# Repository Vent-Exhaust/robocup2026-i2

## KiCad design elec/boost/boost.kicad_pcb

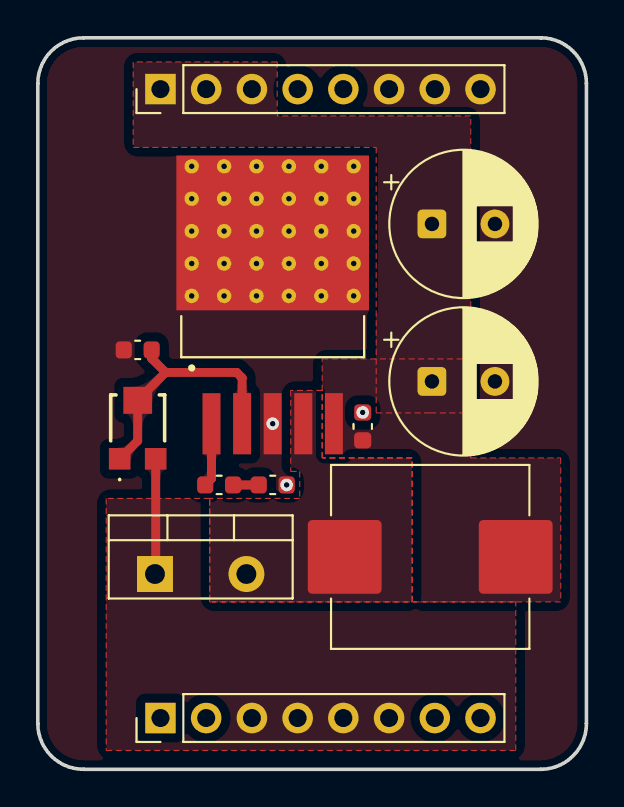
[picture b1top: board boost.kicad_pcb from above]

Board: 2 copper layers, 30.5 x 40.6 mm, 12 parts (0 on the bottom side), 7 nets.

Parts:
C1, C36: 100uF; CP_Radial_D8.0mm_P3.50mm
C35: 0.1uF; C_0603_1608Metric
C40: 0.68uF; C_0603_1608Metric
D2: MBR745; TO-220-2_Vertical
J1, J2: Conn_01x08; PinHeader_1x08_P2.54mm_Vertical
L33: 33uH; L_APV_APH1040
R36: 2K/2.94k; C_0603_1608Metric
R38: 3K; C_0603_1608Metric
U1: LM2587S-ADJ; VREG_TPS79625KTTR
VR1: TC33X-2-104E; TC33X2104E

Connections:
+12V: C1.1, C35.1, C36.1, J1.1, J1.2, J1.3, L33.1, U1.5 (VIN)
+24V: D2.1 (K), J2.3, J2.4, J2.5, J2.6, VR1.3
GND: C1.2, C35.2, C36.2, C40.2, J1.6, J1.7, J1.8, R36.2, U1.3 (GND), U1.6 (GND)
unnamed: C40.1, R38.2
unnamed: D2.2 (A), L33.2, U1.4 (SW)
unnamed: R38.1, U1.1 (COMP)
unnamed: R36.1, U1.2 (FB), VR1.1, VR1.2

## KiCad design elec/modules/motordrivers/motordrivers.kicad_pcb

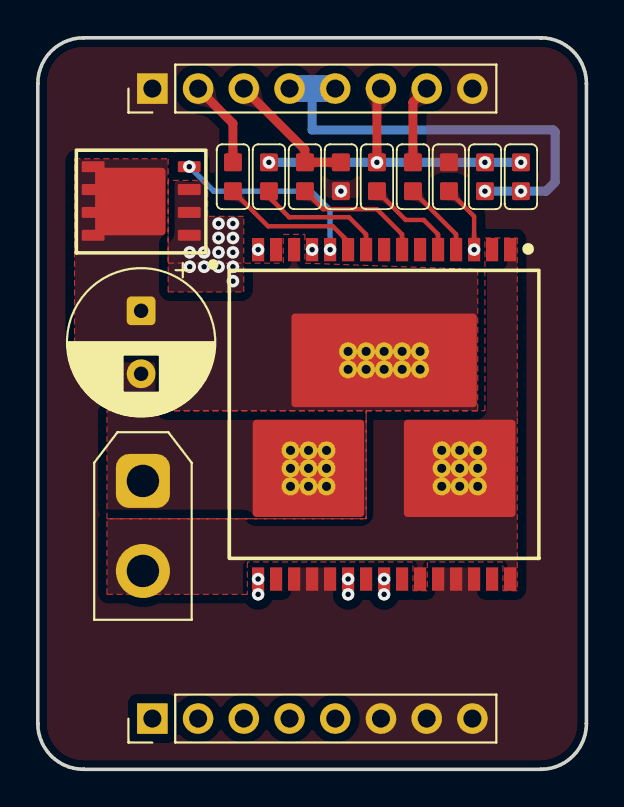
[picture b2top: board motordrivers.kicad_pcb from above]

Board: 2 copper layers, 30.5 x 40.6 mm, 15 parts (0 on the bottom side), 16 nets.

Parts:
C15: 470u; CP_Radial_D8.0mm_P3.50mm
C16: 0u1; Capacitor_0603
IC2: VNH5019ATR-E; VNH5019A-E custom
J1: Conn_01x02; AMASS_XT30UPB-F_1x02_P5.0mm_Vertical
J2, J3: Conn_01x08; PinHeader_1x08_P2.54mm_Vertical
Q1: AON6354; 8-DFN (5x6)withzedot
R8, R9: 3K3; Resistor_0603
R10, R11, R12, R13, R14: 1K; Resistor_0603
R15: 10K; Resistor_0603

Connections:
+3V3: J2.4, J2.5, R8.2, R9.2
+12V: IC2.12 (VBAT), J3.1, J3.2, J3.3, Q1.1 (S), Q1.2 (S), Q1.3 (S)
/CPM1: IC2.11 (CP), Q1.4 (G)
/M IN A: J2.7, R12.1
/M IN B: J2.2, R13.1
/M PWM: J2.3, R14.1, R15.1
/M SW: J2.6, R8.1, R9.1, R10.1, R11.1
/OUT A M: IC2.1 (OUTA), IC2.25 (OUTA), IC2.30 (OUTA), IC2.31 (OUTA), J1.2
/OUT B M: IC2.15 (OUTB), IC2.16 (OUTB), IC2.21 (OUTB), IC2.32 (OUTB), J1.1
GND: C15.2, C16.2, IC2.18 (GND), IC2.19 (GND), IC2.20 (GND), IC2.26 (GND), IC2.27 (GND), IC2.28 (GND), J2.1, J2.8, J3.6, J3.7, J3.8, R15.2
unnamed: C15.1, C16.1, IC2.3 (VCC), IC2.13 (VCC), IC2.23 (VCC), IC2.33 (VCC), Q1.5 (D), Q1.6 (D), Q1.7 (D), Q1.8 (D), Q1.9 (D)
unnamed: IC2.5 (ENA/DIAGA), R10.2
unnamed: IC2.9 (ENB/DIAGB), R11.2
unnamed: IC2.4 (INA), R12.2
unnamed: IC2.10 (INB), R13.2
unnamed: IC2.7 (PWM), R14.2

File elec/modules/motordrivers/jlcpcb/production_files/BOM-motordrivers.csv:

Comment,Designator,Footprint,LCSC,Quantity
0u1,C16,Capacitor_0603,C3011705,1
10K,R15,Resistor_0603,C25804,1
1K,"R10,R11,R12,R13,R14",Resistor_0603,C21190,5
3K3,"R8,R9",Resistor_0603,C22978,2
AON6354,Q1,8-DFN (5x6)withzedot,C22367225,1
VNH5019ATR-E,IC2,VNH5019A-E custom,C2653552,1

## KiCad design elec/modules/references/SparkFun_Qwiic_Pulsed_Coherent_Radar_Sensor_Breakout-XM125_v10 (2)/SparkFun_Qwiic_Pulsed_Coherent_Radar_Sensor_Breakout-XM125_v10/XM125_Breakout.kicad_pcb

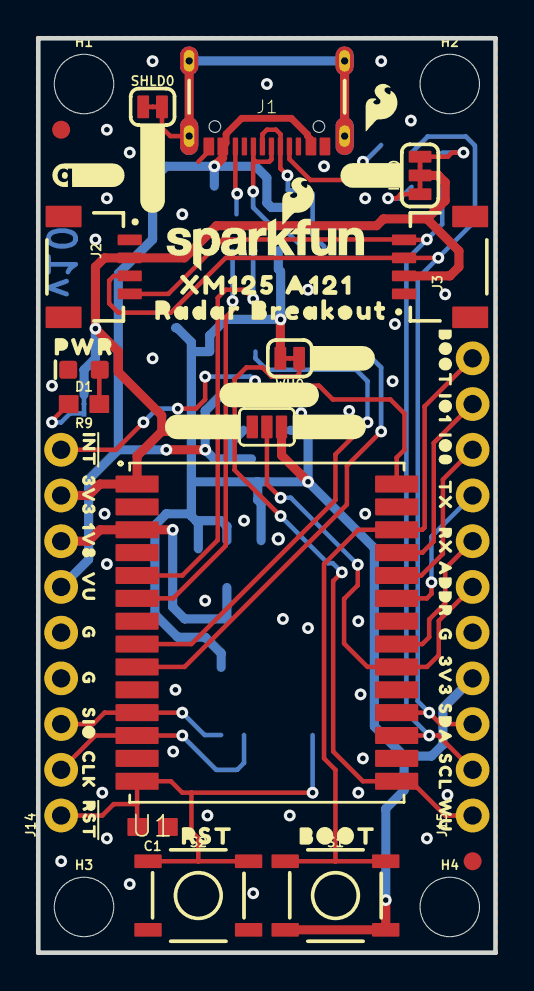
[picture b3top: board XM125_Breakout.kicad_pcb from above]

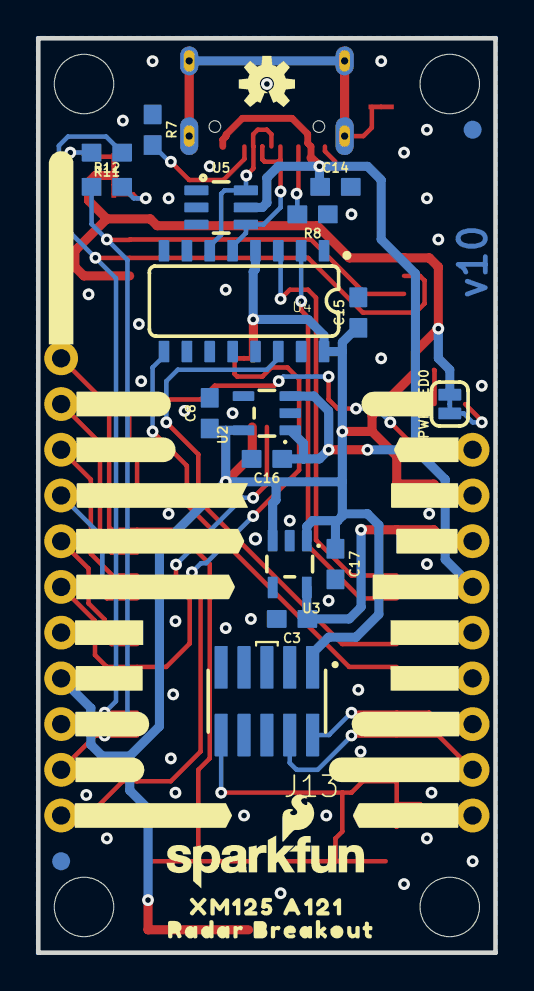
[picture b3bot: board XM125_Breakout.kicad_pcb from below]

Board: 2 copper layers, 25.4 x 50.8 mm, 100 parts (43 on the bottom side), 30 nets.

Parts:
ADDR0: JUMPER-SMT_3_NO_SILK; SMT-JUMPER_3_NO_SILK
C1, C14, C15: 0.1uF; 0603
C3, C8: 22uF; 0603
C16, C17: 2.2uF; 0603
D1: Red; LED-0603
FD1, FD2, FD3, FD4: FIDUCIAL1X2; FIDUCIAL-1X2
FRAME2: FRAME-LETTER; CREATIVE_COMMONS
H1, H2, H3, H4: STAND-OFF
I2C0: JUMPER-SMT_3_2-NC_TRACE_SILK; SMT-JUMPER_3_2-NC_TRACE_SILK
J1: USB-C-16P-2LAYER-PADS
J2, J3: RIGHT_ANGLE; JST04_1MM_RA
J13: SWD (DNP); 2X5-SMD-UNSHROUDED_DNP_NO_PASTE
J14: 1X09_NO_SILK
J15: 1X11_NO_SILK
LOGO1: SPECIAL_INSTRUCTIONS-ORDERING; ORDERING_INSTRUCTIONS
LOGO2: QWIIC_LOGO_4MM; QWIIC_4MM
LOGO3, LOGO6: SFE_LOGO_NAME_FLAME.1_INCH; SFE_LOGO_NAME_FLAME_.1
LOGO4: OSHW-LOGOS; OSHW-LOGO-S
LOGO5: SFE_LOGO_FLAME.1_INCH; SFE_LOGO_FLAME_.1
PWR_LED0: JUMPER-SMT_2_NC_TRACE_SILK; SMT-JUMPER_2_NC_TRACE_SILK
R7, R8: 5.1k; 0603
R9: 4.7k; 0603
R11, R12: 2.2k; 0603
S1, S2: TACTILE_SWITCH_SMD_5.2MM
SHLD0: JUMPER-SMT_2_NC_TRACE_SILK; SMT-JUMPER_2_NC_TRACE_SILK
U1: XM125; XM125_ACC
U2: RT9080-33GJ5; SOT23-5
U3: RT9080-18GJ5; SOT23-5
U4: CH340C; SO016
U5: ESD Diode; SOT-23-6
U$1: #INT143
U$2: ##INT#2
U$3: #LED#139
U$4, U$30, U$31: #GND#141
U$5: RST1630063003525
U$6: RX1152
U$7: #SWDIO#4
U$8: #VUSB#1
U$9: #3V3#17
U$10: #SCL#8
U$11: BOOT21630063003532
U$12: PWR21630063003533
U$13: #SDA#9
U$14, U$33: 3V3144
U$15: 1V8144
U$16: #1V8#141
U$17: RADAR_BREAKOUT1163
U$18: WU9
U$19: #RST6
U$20: #GPIO0#5
U$21: #GPIO1#5
U$22: #WU#14
U$23, U$32: #3V3#141
U$24: XM125_A1211163
U$25: #ADDR#16
U$26: #I2C#126
U$27: #GPIO2##BOOT#141
U$28: #DEBUG_RX#19
U$29: #SHLD#129
U$34, U$35, U$36: G144
U$38: VU146
U$39: IO0147
U$40: IO1148
U$41: BOOT1149
U$42: CLK1150
U$43: #SWDCLK#1151
U$44: TX1153
U$45: ADDR1154
U$46: SDA1155
U$47: SCL1157
U$48: #I2C_ADDR#12
U$49: SIO1159
U$50: #GND#17
U$51: #DEBUG_TX#18
U$53: RADAR_BREAKOUT1166
U$54: XM125_A1211167
U$55: #WAKE_UP#12
U$56: ##RESET#13
WU0: JUMPER-SMT_2_NC_TRACE_SILK; SMT-JUMPER_2_NC_TRACE_SILK

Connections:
1.8V: C3.1, J14.7, U1.3, U3.5
3.3V: ADDR0.3, C8.1, C15.1, C17.1, I2C0.2, J2.2, J3.2, J13.1, J14.8, J15.4, PWR_LED0.2, S1.3, S1.4, U1.1, U2.5, U3.1, U3.3, U4.4, U4.16, WU0.2
CH340-CTS: U1.9, U4.9
CH340-RTS: U1.8, U4.14
CH340-RX: U1.5, U4.3
CH340-TX: U1.6, U4.2
DEBUG_UART-RX: J15.7, U1.21
DEBUG_UART-TX: J15.8, U1.23
GND: ADDR0.1, C1.1, C3.2, C8.2, C14.2, C15.2, C16.2, C17.2, D1.C, J1.GND, J1.GND2, J2.1, J3.1, J13.3, J13.5, J13.9, J14.4, J14.5, J15.5, R7.1, R8.1, S2.3, S2.4, SHLD0.1, U1.2, U1.4, U1.7, U1.10, U1.13, U1.16, U1.19, U1.22, U1.27, U2.2, U3.2, U4.1, U5.2
unnamed: J1.A6, J1.B6, U4.5, U5.4
unnamed: J1.A7, J1.B7, U4.6, U5.6
unnamed: J1.SHLD1, J1.SHLD2, J1.SHLD3, J1.SHLD4, SHLD0.2
unnamed: J1.B5, R8.2
unnamed: J1.A5, R7.2
unnamed: PWR_LED0.1, R9.2
unnamed: D1.A, R9.1
unnamed: I2C0.3, R11.2
unnamed: I2C0.1, R12.2
SCL: J2.4, J3.4, J15.2, R12.1, U1.17
SDA: J2.3, J3.3, J15.3, R11.1, U1.18
SWD_CLK: J13.4, J14.2, U1.12
SWD_IO: J13.2, J14.3, U1.11
V_USB: C14.1, C16.1, J1.VBUS1, J1.VBUS2, J14.6, U2.1, U2.3, U5.5
WAKE_UP: J15.1, U1.15, WU0.1
XM125_GPIO0: J15.9, U1.24
XM125_GPIO1: J15.10, U1.25
XM125_GPIO2/BOOT0: J15.11, S1.1, S1.2, U1.26
XM125_I2C_ADDRESS: ADDR0.2, J15.6, U1.20
~XM125_INT: J14.9, U1.28
~XM125_RESET: C1.2, J13.10, J14.1, S2.1, S2.2, U1.14

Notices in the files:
parts and their libraries:
Released under the Creative Commons Attribution Share-Alike 4.0 License
https://creativecommons.org/licenses/by-sa/4.0
